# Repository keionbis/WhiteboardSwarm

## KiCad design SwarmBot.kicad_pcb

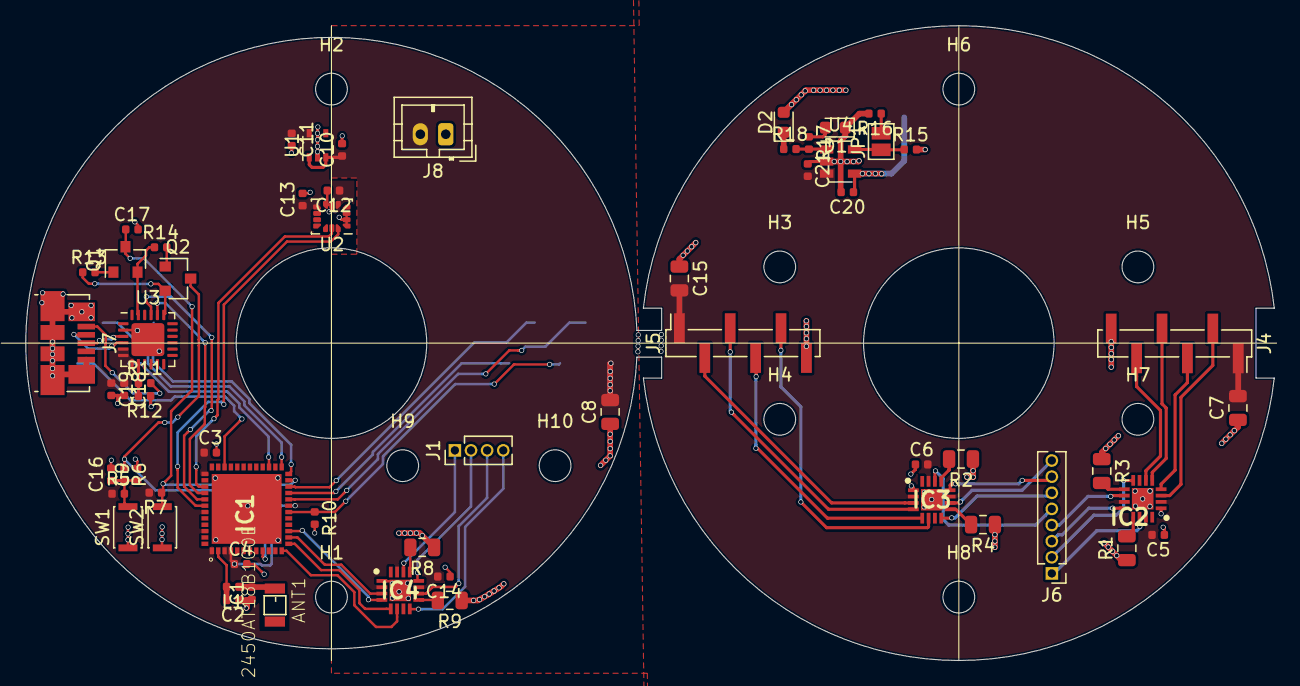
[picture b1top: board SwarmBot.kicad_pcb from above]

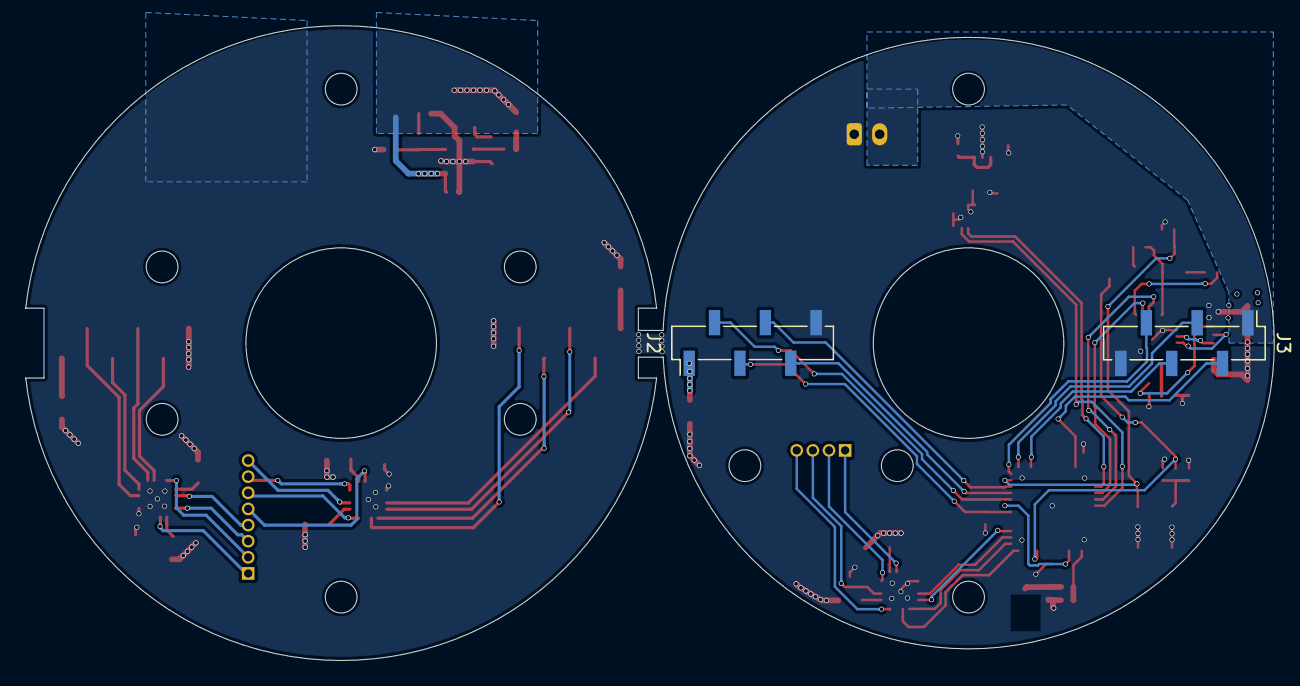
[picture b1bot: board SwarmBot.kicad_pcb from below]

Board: 2 copper layers, 98.3 x 50.0 mm, 74 parts (2 on the bottom side), 63 nets.

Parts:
ANT1: 2450AT18B100E; ANT_2450AT18B100E
C1, C2, C3, C4, C5, C6, C9, C10, C11, C12, C13, C14, C16, C17, C18, C19, C20, C21: C; C_0402_1005Metric
C7, C8, C15: C; C_0805_2012Metric
D1, D2: LED; LED_0603_1608Metric
H1, H2, H3, H4, H5, H6, H7, H8, H9, H10: MountingHole; MountingHole_2.5mm
IC1: ESP32-PICO-D4; ESP32-PICO-D4_1
IC2, IC3, IC4: A3916GESTR-T; QFN50P300X300X75-17N-D
J1: Conn_01x04_Female; PinHeader_1x04_P1.27mm_Vertical
J2, J3: Conn_01x06_Female; PinSocket_1x06_P2.00mm_Vertical_SMD_Pin1Left
J4, J5: Conn_01x06_Female; PinHeader_1x06_P2.00mm_Vertical_SMD_Pin1Right
J6: Conn_01x08_Female; PinHeader_1x08_P1.27mm_Vertical
J7: USB_B_Micro; USB_Micro-B_Molex_47346-0001
J8: Conn_01x02_Male; JST_PH_B2B-PH-K_1x02_P2.00mm_Vertical
JP1: Jumper_NO_Small; SolderJumper-2_P1.3mm_Open_Pad1.0x1.5mm
L1: L; L_0402_1005Metric
Q1, Q2: MMBT3904; SOT-23
R1, R2, R3, R4, R8, R9: R; R_0805_2012Metric
R5, R6, R7, R10, R11, R12, R13, R14, R15, R16, R17, R18: R; R_0402_1005Metric
SW1, SW2: SW_Push_Open; SW_SPST_CK_KXT3
U1: MIC5366-3.3YC5; SOT-353_SC-70-5
U2: LSM6DS3; LGA-14_3x2.5mm_P0.5mm_LayoutBorder3x4y
U3: CP2102N-A01-GQFN24; QFN-24-1EP_4x4mm_P0.5mm_EP2.6x2.6mm
U4: MCP73831-2-OT; SOT-23-5

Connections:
+3V3: C3.1, C4.1, C11.1, C12.1, C13.1, C18.1, C19.1, IC1.1, IC1.3, IC1.4, IC1.19, IC1.37, IC1.43, IC1.46, R5.1, R7.2, U1.5, U2.5, U2.8, U3.5, U3.6, U3.7
+5V: C20.1, D2.2, J7.1, R11.2, U4.4
+BATT: C5.2, C6.2, C7.2, C8.2, C10.1, C14.2, C15.2, C21.2, IC2.2, IC2.11, IC2.15, IC3.2, IC3.11, IC3.15, IC4.2, IC4.11, IC4.15, J2.1, J3.1, J4.1, J5.1, J8.2, U1.1, U1.3, U4.3
/Sheet5DAF9EB0/A1_3: IC4.14, J1.1
/Sheet5DAF9EB0/A2_3: IC4.8, J1.4
/Sheet5DAF9EB0/B1_3: IC4.12, J1.2
/Sheet5DAF9EB0/B2_3: IC4.10, J1.3
/Sheet5DAF9EB0/DTR: Q1.2, R14.1, U3.23
/Sheet5DAF9EB0/D_N: J7.2, U3.4
/Sheet5DAF9EB0/D_P: J7.3, U3.3
/Sheet5DAF9EB0/EN: IC1.9, Q2.3, R6.1
/Sheet5DAF9EB0/IO0: C17.1, IC1.23, Q1.3, R7.1, SW2.2
/Sheet5DAF9EB0/M1A: IC1.20, J2.2
/Sheet5DAF9EB0/M1A_2: IC1.34, J3.2
/Sheet5DAF9EB0/M1A_3: IC1.14, IC4.3
/Sheet5DAF9EB0/M1B: IC1.18, J2.3, R10.1
/Sheet5DAF9EB0/M1B_2: IC1.25, J3.3
/Sheet5DAF9EB0/M1B_3: IC1.15, IC4.4
/Sheet5DAF9EB0/M2A: IC1.22, J2.4
/Sheet5DAF9EB0/M2A_2: IC1.27, J3.4
/Sheet5DAF9EB0/M2A_3: IC1.13, IC4.5
/Sheet5DAF9EB0/M2B: IC1.21, J2.5
/Sheet5DAF9EB0/M2B_2: IC1.24, J3.5
/Sheet5DAF9EB0/M2B_3: IC1.12, IC4.6
/Sheet5DAF9EB0/RTS: Q2.2, R13.1, U3.19
/Sheet5DAF9EB0/RX: IC1.40, U3.20
/Sheet5DAF9EB0/SCL: IC1.39, U2.13
/Sheet5DAF9EB0/SDA: IC1.42, U2.14
/Sheet5DAF9EB0/TX: IC1.41, U3.21
/Sheet5DAF9EF1/A1: IC2.14, J6.1
/Sheet5DAF9EF1/A1_2: IC3.14, J6.5
/Sheet5DAF9EF1/A2: IC2.8, J6.2
/Sheet5DAF9EF1/A2_2: IC3.8, J6.6
/Sheet5DAF9EF1/B1: IC2.12, J6.3
/Sheet5DAF9EF1/B1_2: IC3.12, J6.7
/Sheet5DAF9EF1/B2: IC2.10, J6.4
/Sheet5DAF9EF1/B2_2: IC3.10, J6.8
/Sheet5DAF9EF1/M1A: IC2.3, J4.2
/Sheet5DAF9EF1/M1A_2: IC3.3, J5.2
/Sheet5DAF9EF1/M1B: IC2.4, J4.3
/Sheet5DAF9EF1/M1B_2: IC3.4, J5.3
/Sheet5DAF9EF1/M2A: IC2.5, J4.4
/Sheet5DAF9EF1/M2A_2: IC3.5, J5.4
/Sheet5DAF9EF1/M2B: IC2.6, J4.5
/Sheet5DAF9EF1/M2B_2: IC3.6, J5.5
GND: C1.1, C2.1, C3.2, C4.2, C5.1, C6.1, C7.1, C8.1, C9.2, C10.2, C11.2, C12.2, C13.2, C14.1, C15.1, C16.2, C17.2, C18.2, C19.2, C20.2, C21.1, D1.1, IC1.49, IC2.1, IC2.17, IC3.1, IC3.17, IC4.1, IC4.17, J2.6, J3.6, J4.6, J5.6, J7.5, J7.6, J8.1, R1.1, R2.1, R3.1, R4.1, R8.1, R9.1, R10.2, R12.1, R15.2, R16.2, SW1.1, SW2.1, U1.2, U2.1, U2.2, U2.3, U2.6, U2.7, U3.2, U3.25, U4.2
unnamed: ANT1.1, C1.2, L1.1
unnamed: C2.2, IC1.2, L1.2
unnamed: C9.1, C16.1, R5.2, R6.2, SW1.2
unnamed: D1.2, R17.1
unnamed: D2.1, R18.1
unnamed: IC2.9, R3.2
unnamed: IC2.13, R1.2
unnamed: IC3.9, R4.2
unnamed: IC3.13, R2.2
unnamed: IC4.9, R9.2
unnamed: IC4.13, R8.2
unnamed: JP1.1, R15.1, U4.5
unnamed: JP1.2, R16.1
unnamed: Q1.1, R13.2
unnamed: Q2.1, R14.2
unnamed: R11.1, R12.2, U3.8
unnamed: R17.2, R18.2, U4.1

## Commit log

2019-10-24 initial push
2019-10-24 correct according to cad
2019-10-26 routed and reshaped
